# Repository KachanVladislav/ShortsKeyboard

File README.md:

# ShortsKeyboard v1.0

## Описание

Клавиатура для переключения видео - вперед/назад посредством встряски.

* ./3dmodel/ShortsKeyboardCase.FCStd - модель корпуса, в реальности USB подуключил сзади, спереди кнопка включения
* ./3dmodel/TumblerPowerOn.FCStd - кнопка включения (in process)
* ./shortKeyboard_sch/ - принципиальная схема + печатная плата основного модуля
* ./powerSwitch_sch/ - печатная плата кнопки включения - не влезла в корпус (tbd)

## Блок-схема

## График ускорения при встряске

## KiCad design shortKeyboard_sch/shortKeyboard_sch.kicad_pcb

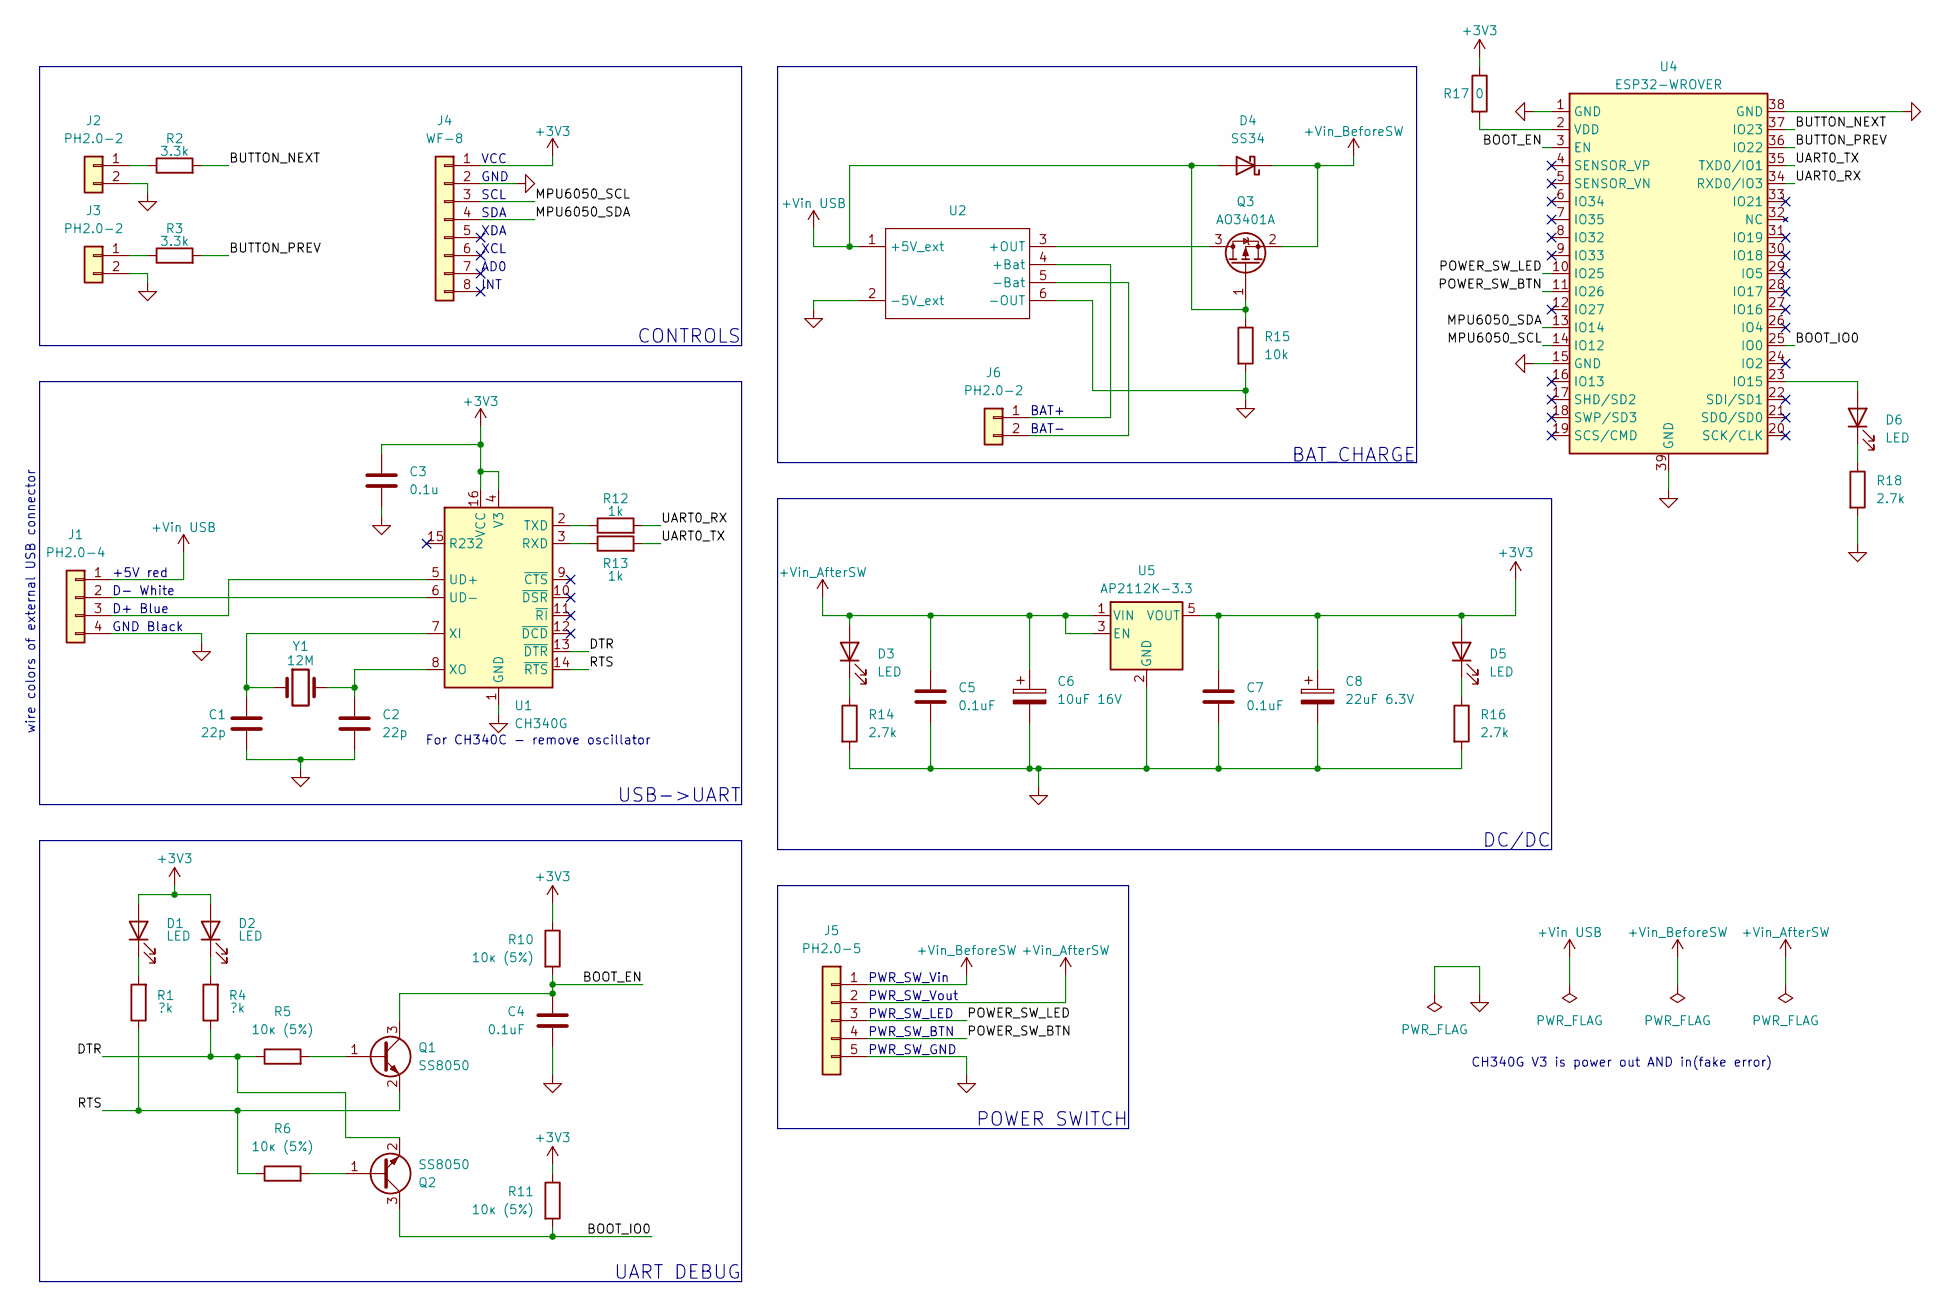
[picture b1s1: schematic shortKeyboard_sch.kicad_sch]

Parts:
C1, C2: 22p; C_0805_2012Metric_Pad1.18x1.45mm_HandSolder
C3: 0.1u; C_0805_2012Metric_Pad1.18x1.45mm_HandSolder
C4, C5, C7: 0.1uF; C_0805_2012Metric_Pad1.18x1.45mm_HandSolder
C6: 10uF 16V; CP_EIA-3216-18_Kemet-A_HandSolder
C8: 22uF 6.3V; CP_EIA-3216-18_Kemet-A_HandSolder
D1, D2, D3, D5, D6: LED; LED_0805_2012Metric_Pad1.15x1.40mm_HandSolder
D4: SS34; D_SMA
J1: PH2.0-4
J2, J3, J6: PH2.0-2
J4: WF-8
J5: PH2.0-5
Q1, Q2: SS8050; SOT-23
Q3: AO3401A; SOT-23
R1, R4: ?k; R_0805_2012Metric_Pad1.20x1.40mm_HandSolder
R2, R3: 3.3k; R_0805_2012Metric_Pad1.20x1.40mm_HandSolder
R5, R6, R10, R11: 10к (5%); R_0805_2012Metric_Pad1.20x1.40mm_HandSolder
R12, R13: 1k; R_0805_2012Metric_Pad1.20x1.40mm_HandSolder
R14, R16, R18: 2.7k; R_0805_2012Metric_Pad1.20x1.40mm_HandSolder
R15: 10k; R_0805_2012Metric_Pad1.20x1.40mm_HandSolder
R17: 0; R_0805_2012Metric_Pad1.20x1.40mm_HandSolder
U1: CH340G; SOIC-16_3.9x9.9mm_P1.27mm
U2: TP4056_Module_CD_MicroUsb
U4: ESP32-WROVER; ESP32-WROVER-handSoldering
U5: AP2112K-3.3; SOT-23-5
Y1: 12M; Crystal_SMD_HC49-SD_HandSoldering

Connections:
+3V3: C3.1, C7.1, C8.1, D1.2 (A), D2.2 (A), D5.2 (A), J4.1, R10.1, R11.1, R17.1, U1.4 (V3), U1.16 (VCC), U5.5 (VOUT)
+Vin USB: D4.2 (A), J1.1, Q3.1 (G), R15.1, U2.1 (+5V_ext)
+Vin_AfterSW: C5.1, C6.1, D3.2 (A), J5.2 (Pin_1), U5.1 (VIN), U5.3 (EN)
+Vin_BeforeSW: D4.1 (K), J5.1, Q3.2 (S)
/Корневой лист/BOOT_EN: C4.1, Q1.3 (C), R10.2, U4.3 (EN)
/Корневой лист/BOOT_IO0: Q2.3 (C), R11.2, U4.25 (IO0)
/Корневой лист/BUTTON_NEXT: R2.2, U4.37 (IO23)
/Корневой лист/BUTTON_PREV: R3.2, U4.36 (IO22)
/Корневой лист/DTR: Q2.2 (E), R4.1, R5.1, U1.13 (~DTR)
/Корневой лист/MPU6050_SCL: J4.3, U4.14 (IO12)
/Корневой лист/MPU6050_SDA: J4.4, U4.13 (IO14)
/Корневой лист/POWER_SW_BTN: J5.4 (Pin_1), U4.11 (IO26)
/Корневой лист/POWER_SW_LED: J5.3 (Pin_2), U4.10 (IO25)
/Корневой лист/RTS: Q1.2 (E), R1.1, R6.1, U1.14 (~RTS)
/Корневой лист/UART0_RX: R12.2, U4.34 (RXD0/IO3)
/Корневой лист/UART0_TX: R13.2, U4.35 (TXD0/IO1)
GND: C1.2, C2.2, C3.2, C4.2, C5.2, C6.2, C7.2, C8.2, J1.4 (Pin_1), J2.2, J3.2, J4.2, J5.5 (Pin_1), R14.2, R15.2, R16.2, R18.2, U1.1 (GND), U2.2 (-5V_ext), U2.6 (-OUT), U4.1 (GND), U4.15 (GND), U4.38 (GND), U4.39 (GND), U5.2 (GND)
unnamed: D1.1 (K), R1.2
unnamed: D2.1 (K), R4.2
unnamed: D3.1 (K), R14.1
unnamed: D5.1 (K), R16.1
unnamed: D6.2 (A), U4.23 (IO15)
unnamed: D6.1 (K), R18.1
unnamed: J1.3 (Pin_2), U1.5 (UD+)
unnamed: J2.1, R2.1
unnamed: J3.1, R3.1
unnamed: J6.1, U2.4 (+Bat)
unnamed: J6.2, U2.5 (-Bat)
unnamed: Q1.1 (B), R5.2
unnamed: Q2.1 (B), R6.2
unnamed: Q3.3 (D), U2.3 (+OUT)
unnamed: R13.1, U1.3 (RXD)
unnamed: R12.1, U1.2 (TXD)
unnamed: J1.2 (Pin_1), U1.6 (UD-)
unnamed: C1.1, U1.7 (XI), Y1.1
unnamed: C2.1, U1.8 (XO), Y1.2
unnamed: R17.2, U4.2 (VDD)

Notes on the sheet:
BAT_CHARGE
INT
PWR_SW_LED
PWR_SW_GND
SDA
POWER SWITCH
GND Black
CONTROLS
XDA
UART DEBUG
SCL
For CH340C - remove oscillator
PWR_SW_Vout
DC/DC
BAT-
GND
VCC
D- White
PWR_SW_BTN
XCL
CH340G V3 is power out AND in(fake error)
PWR_SW_Vin
D+ Blue
AD0
+5V red
USB->UART
BAT+
wire colors of external USB connector

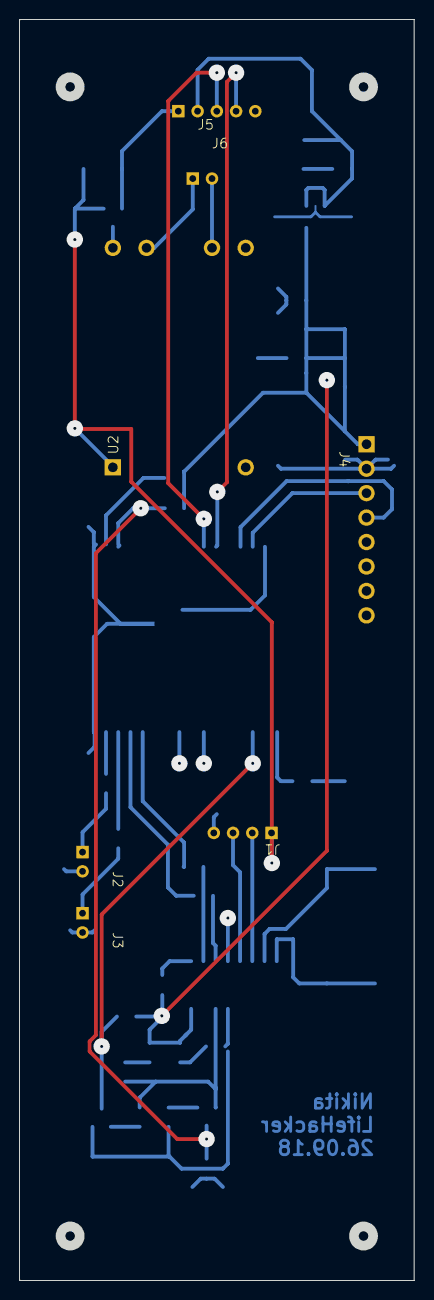
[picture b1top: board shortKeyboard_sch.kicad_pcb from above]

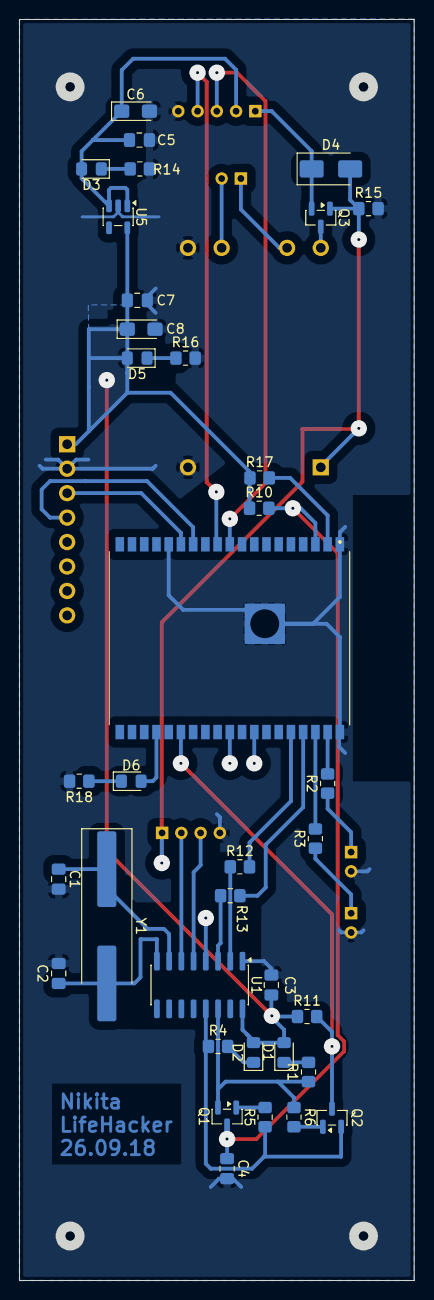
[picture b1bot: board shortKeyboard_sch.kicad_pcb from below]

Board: 2 copper layers, 41.0 x 131.0 mm, 43 parts (36 on the bottom side), 37 nets.
